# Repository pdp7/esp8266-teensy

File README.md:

Test of ESP-01 breakout for ESP8266 with Teensy LC 

* OSH Park Shared Project
   * https://oshpark.com/shared_projects/4drkvDoA

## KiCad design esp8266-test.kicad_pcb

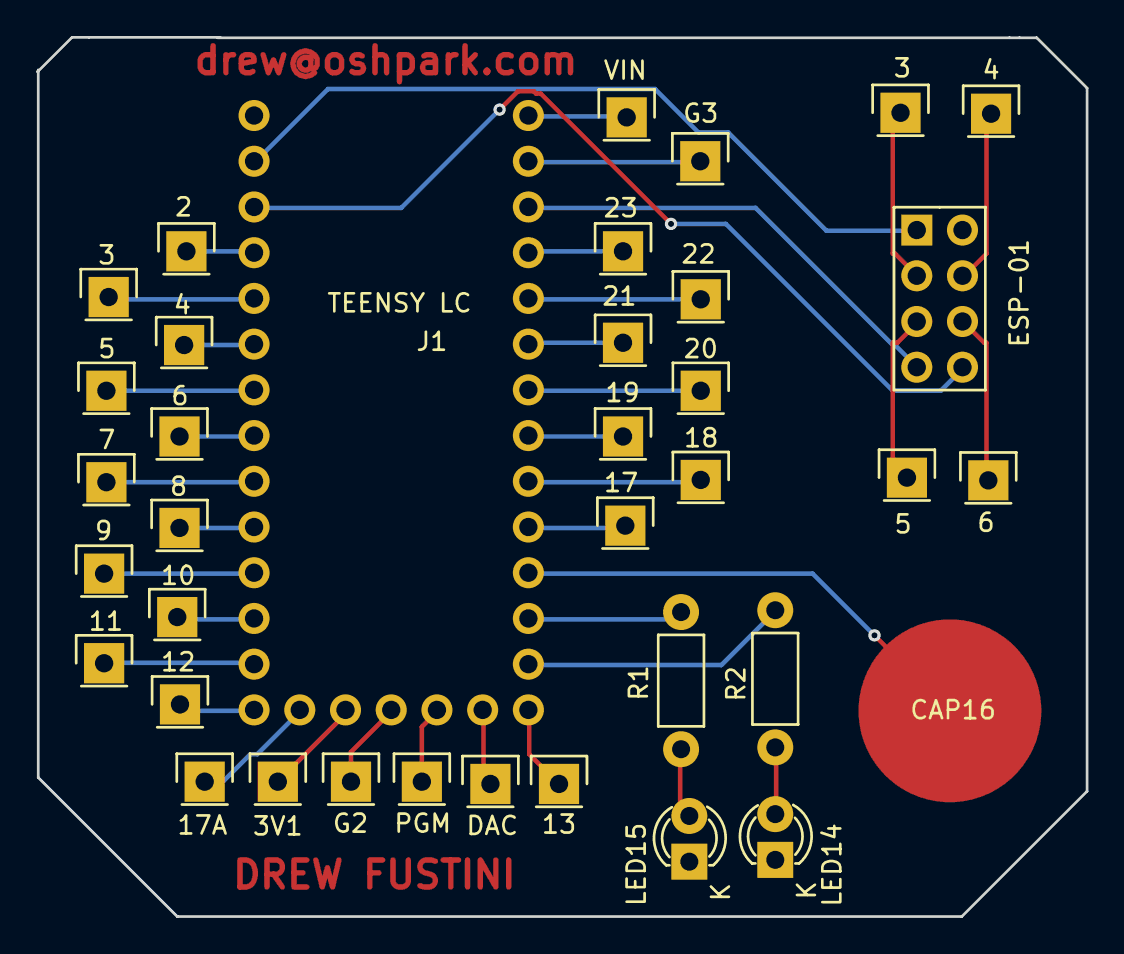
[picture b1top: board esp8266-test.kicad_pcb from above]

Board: 2 copper layers, 58.3 x 48.8 mm, 37 parts (0 on the bottom side), 39 nets.

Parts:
2, 3, 3#2, 3V1, 4, 4#2, 5, 5#2, 6, 6#2, 7, 8, 9, 10, 11, 12, 13, 17, 17A, 18, 19, 20, 21, 22, 23: HEADER-MALE-1POS-TH-1x01; Pin_Header_Straight_1x01
CAP16: CAPSENSE_CIRCLE; CAPSENSE_CIRCLE_D10
DAC: HEADER-MALE-1POS-TH-1x01; Pin_Header_Straight_1x01
ESP-01: ESP-01v090; ESP-01
G2, G3: HEADER-MALE-1POS-TH-1x01; Pin_Header_Straight_1x01
J1: TEENSY-LC
LED14, LED15: LED; LED-3MM-2PIN
PGM: HEADER-MALE-1POS-TH-1x01; Pin_Header_Straight_1x01
R1, R2: R; Resistor_Horizontal_RM7mm
VIN: HEADER-MALE-1POS-TH-1x01; Pin_Header_Straight_1x01

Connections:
unnamed: CAP16.1, J1.16
unnamed: ESP-01.2, J1.G1, LED14.1, LED15.1
unnamed: LED15.2, R1.1
unnamed: LED14.2, R2.1
unnamed: ESP-01.1, J1.0
unnamed: ESP-01.8, J1.1
unnamed: 2.1, J1.2
unnamed: 3.1, J1.3
unnamed: 3V1.1, J1.3V1
unnamed: ESP-01.7, J1.3V2
unnamed: 4.1, J1.4
unnamed: 5.1, J1.5
unnamed: 6.1, J1.6
unnamed: 7.1, J1.7
unnamed: 8.1, J1.8
unnamed: 9.1, J1.9
unnamed: 10.1, J1.10
unnamed: 11.1, J1.11
unnamed: 12.1, J1.12
unnamed: 13.1, J1.13
unnamed: J1.14, R2.2
unnamed: J1.15, R1.2
unnamed: 17.1, J1.17
unnamed: 17A.1, J1.17A
unnamed: 18.1, J1.18
unnamed: 19.1, J1.19
unnamed: 20.1, J1.20
unnamed: 21.1, J1.21
unnamed: 22.1, J1.22
unnamed: 23.1, J1.23
unnamed: DAC.1, J1.DAC
unnamed: G2.1, J1.G2
unnamed: G3.1, J1.G3
unnamed: J1.PGM, PGM.1
unnamed: J1.VIN, VIN.1
unnamed: 3#2.1, ESP-01.3
unnamed: 5#2.1, ESP-01.5
unnamed: 4#2.1, ESP-01.4
unnamed: 6#2.1, ESP-01.6

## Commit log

2016-07-20 initial design files
2016-07-20 update layout
